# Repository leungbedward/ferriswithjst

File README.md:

# Sweep Half Swept

Half of a Sweep2 with a reversible micro-controller footprint with a Surface Mount JST connector

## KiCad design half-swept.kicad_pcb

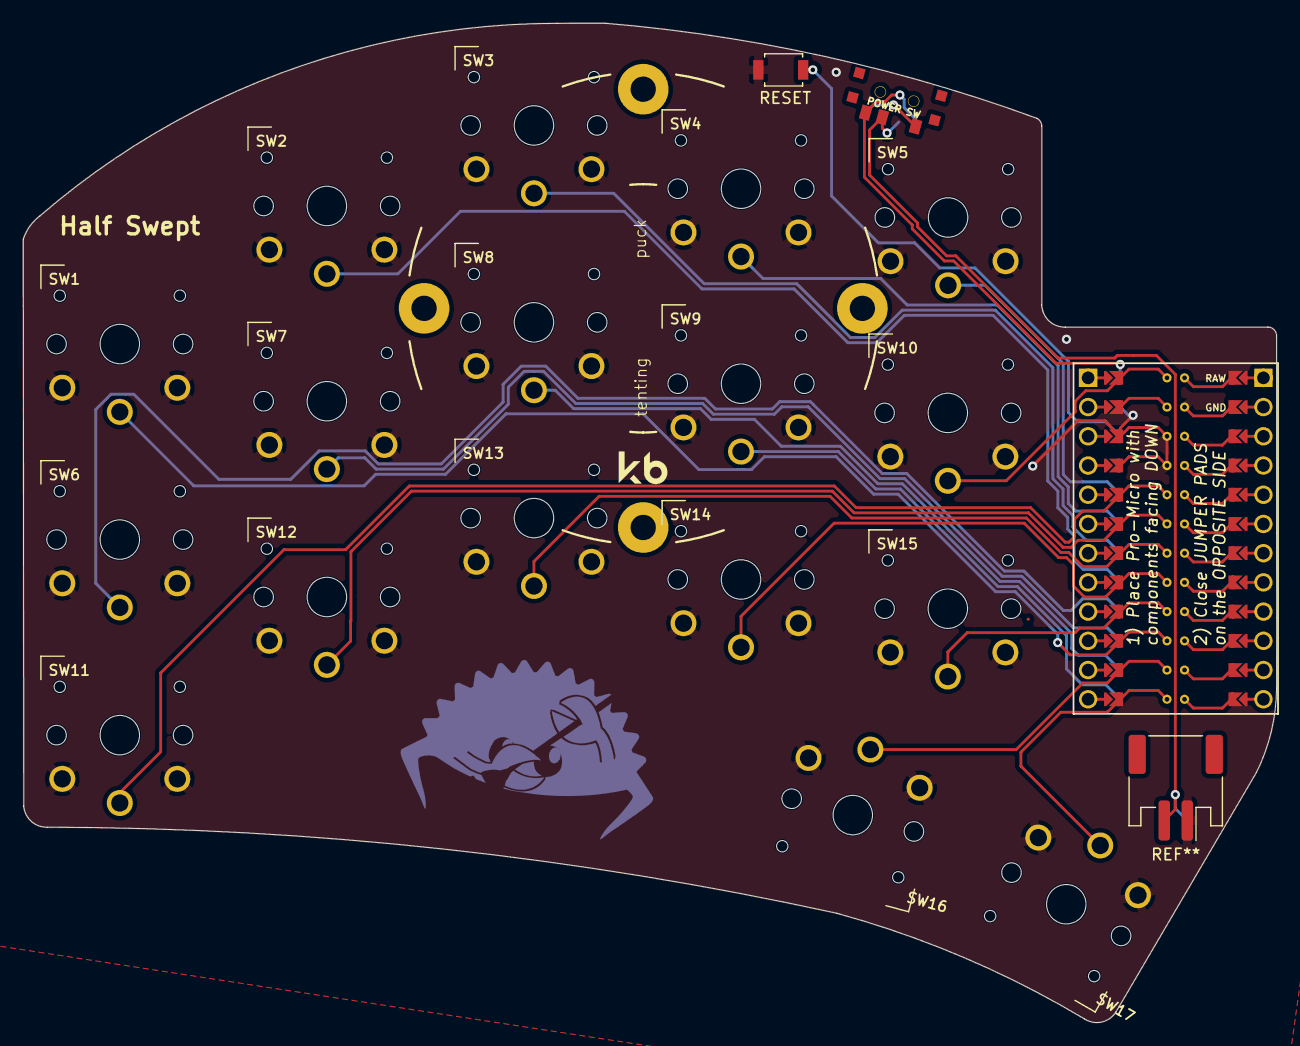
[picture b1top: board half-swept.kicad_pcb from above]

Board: 2 copper layers, 109.0 x 86.9 mm, 20 parts (0 on the bottom side), 20 nets.

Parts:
POWER SW: SW_SPDT; SPDT_C128955
RSW2: SW_Push; Tactile-Switch_SMT
SW1, SW2, SW3, SW4, SW5, SW6, SW7, SW8, SW9, SW10, SW11, SW12, SW13, SW14, SW15, SW16, SW17: SW_Push; SW_PG1350_rev_DPB
U1: ProMicro-kbd; ProMicro_jumpers_facedown

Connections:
Switch1: SW1.1, U1.10
Switch2: SW2.1, U1.17
Switch3: SW3.1, U1.18
Switch4: SW4.1, U1.19
Switch5: SW5.1, U1.20
Switch6: SW6.1, U1.16
Switch7: SW7.1, U1.15
Switch8: SW8.1, U1.14
Switch9: SW9.1, U1.13
Switch10: SW10.1, U1.1
Switch11: SW11.1, U1.5
Switch12: SW12.1, U1.6
Switch13: SW13.1, U1.7
Switch14: SW14.1, U1.8
Switch15: SW15.1, U1.9
Switch16: SW16.1, U1.11
Switch17: SW17.1, U1.12
gnd: RSW2.1, RSW2.2, SW1.2, SW2.2, SW3.2, SW4.2, SW5.2, SW6.2, SW7.2, SW8.2, SW9.2, SW10.2, SW11.2, SW12.2, SW13.2, SW14.2, SW15.2, SW16.2, SW17.2, U1.3, U1.4, U1.23
raw: POWER SW.3, U1.24
reset: RSW2.1, RSW2.2, U1.22
